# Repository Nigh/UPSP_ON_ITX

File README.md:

# Up Squared Pro ITX转接板

主页：https://up-board.org/up-squared-pro/

HW Spec：https://github.com/up-board/up-community/wiki/Hardware_Specification_UPS_Pro

Pinout：https://github.com/up-board/up-community/wiki/Pinout_UPSPro

本项目为将Up Squared Pro转接到ITX规格的PCB工程

## PCB配置

- 固定UPSP的孔位
- ATX-24插座
- USB-A供电口 x4
- USB-C供电口 x1
- USB常电供电口 x3
- 12V 电池插座 x2
- 12V 5.5x2.1供电插座 x2
- UPSP 12V 供电焊盘
- ATX电源供电开关
- UPSP开关
- 电源灯排针(5v pwr_ok)
- 电源使能接口

## 电源输出能力

- `+12v`:15A
- `+5v`:18A
- `+3.3v`:22A
- `+5vSB`:2A
- `-5v`:0.5A
- `-12v`:0.5A

## 笔记

### ATX-24

`PS_ON`短接到`GND`时，电源开始工作。否则，只有`5VSB`口输出。

`PWR_OK`是电源输出稳定的信号。当电源输出达到稳定状态后，会输出`5V`。一般在电源开始工作100ms-500ms后这个信号将会给出。

这里的实践将直接采用一个船型开关接到`PS_ON`的方式来控制电源。

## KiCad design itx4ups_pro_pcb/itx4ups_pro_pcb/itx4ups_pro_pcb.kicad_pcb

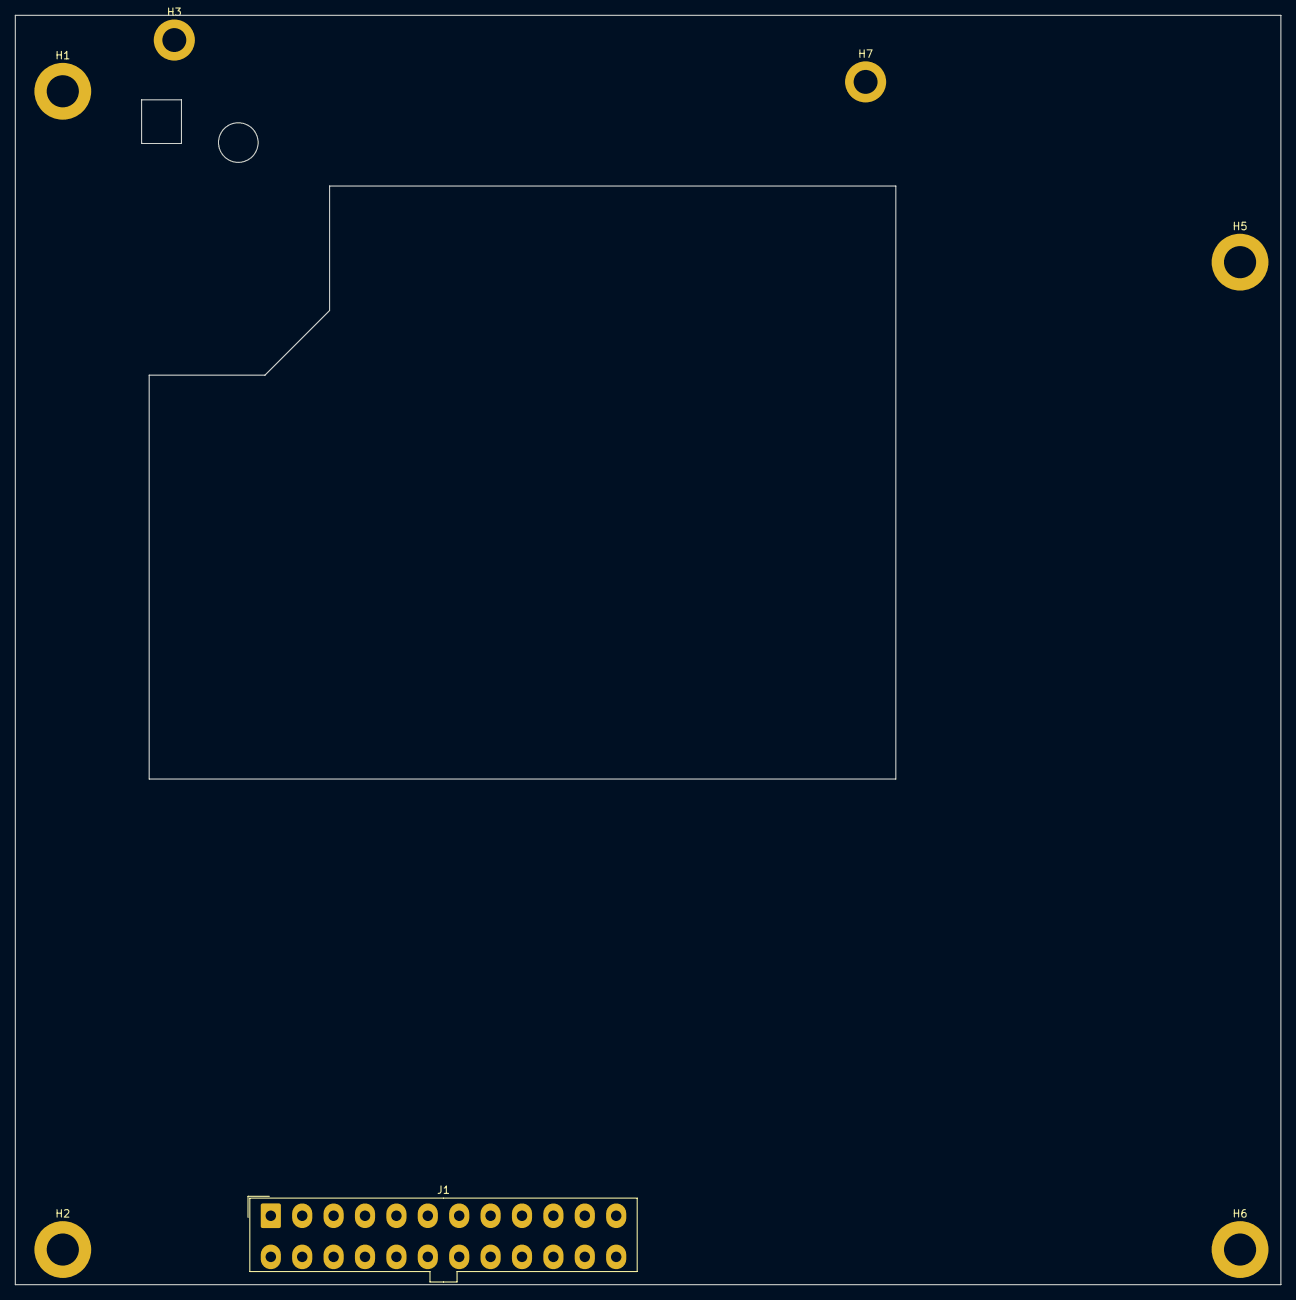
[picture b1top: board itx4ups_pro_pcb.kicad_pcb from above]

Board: 2 copper layers, 169.3 x 169.8 mm, 8 parts (0 on the bottom side), 4 nets, no tracks yet.

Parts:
H1, H2, H5, H6: ITX_Hole; MountingHole_4.3mm_M4_ISO7380_Pad
H3, H7: UpBoard_Hole; MountingHole_3.2mm_M3_ISO14580_Pad
H4: UpBoard_Hole; MountingHole_5.3mm_M5_ISO14580
J1: ATX-24; Molex_Mini-Fit_Jr_5566-24A_2x12_P4.20mm_Vertical

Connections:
unnamed: J1.1 (+3.3V), J1.2 (+3.3V), J1.12 (+3.3V), J1.13 (+3.3V)
unnamed: J1.10 (+12V), J1.11 (+12V)
unnamed: J1.3 (GND), J1.5 (GND), J1.7 (GND), J1.15 (GND), J1.17 (GND), J1.18 (GND), J1.19 (GND), J1.24 (GND)
unnamed: J1.4 (+5V), J1.6 (+5V), J1.21 (+5V), J1.22 (+5V), J1.23 (+5V)

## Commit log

2022-03-03 pcb added
2022-03-03 [ImgBot] Optimize images
    *Total -- 256.29kb -> 187.20kb (26.96%)
    /itx4ups_pro_pcb_bottom.png -- 121.30kb -> 85.78kb (29.29%)
    /itx4ups_pro_pcb_top.png -- 134.98kb -> 101.42kb (24.87%)
